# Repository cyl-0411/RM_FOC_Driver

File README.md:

# 更新日志

## [<1.2.0-beta>] - <2023.1.1>

### <电流采样方案更新>

* 变更	：更新为采集相电流

* 变更	：更新采样芯片

### <移除>

* 移除`MCU	`
* 将编码器独立到另一块`PCB`上

### <存在问题>

* 工作时电机会啸叫

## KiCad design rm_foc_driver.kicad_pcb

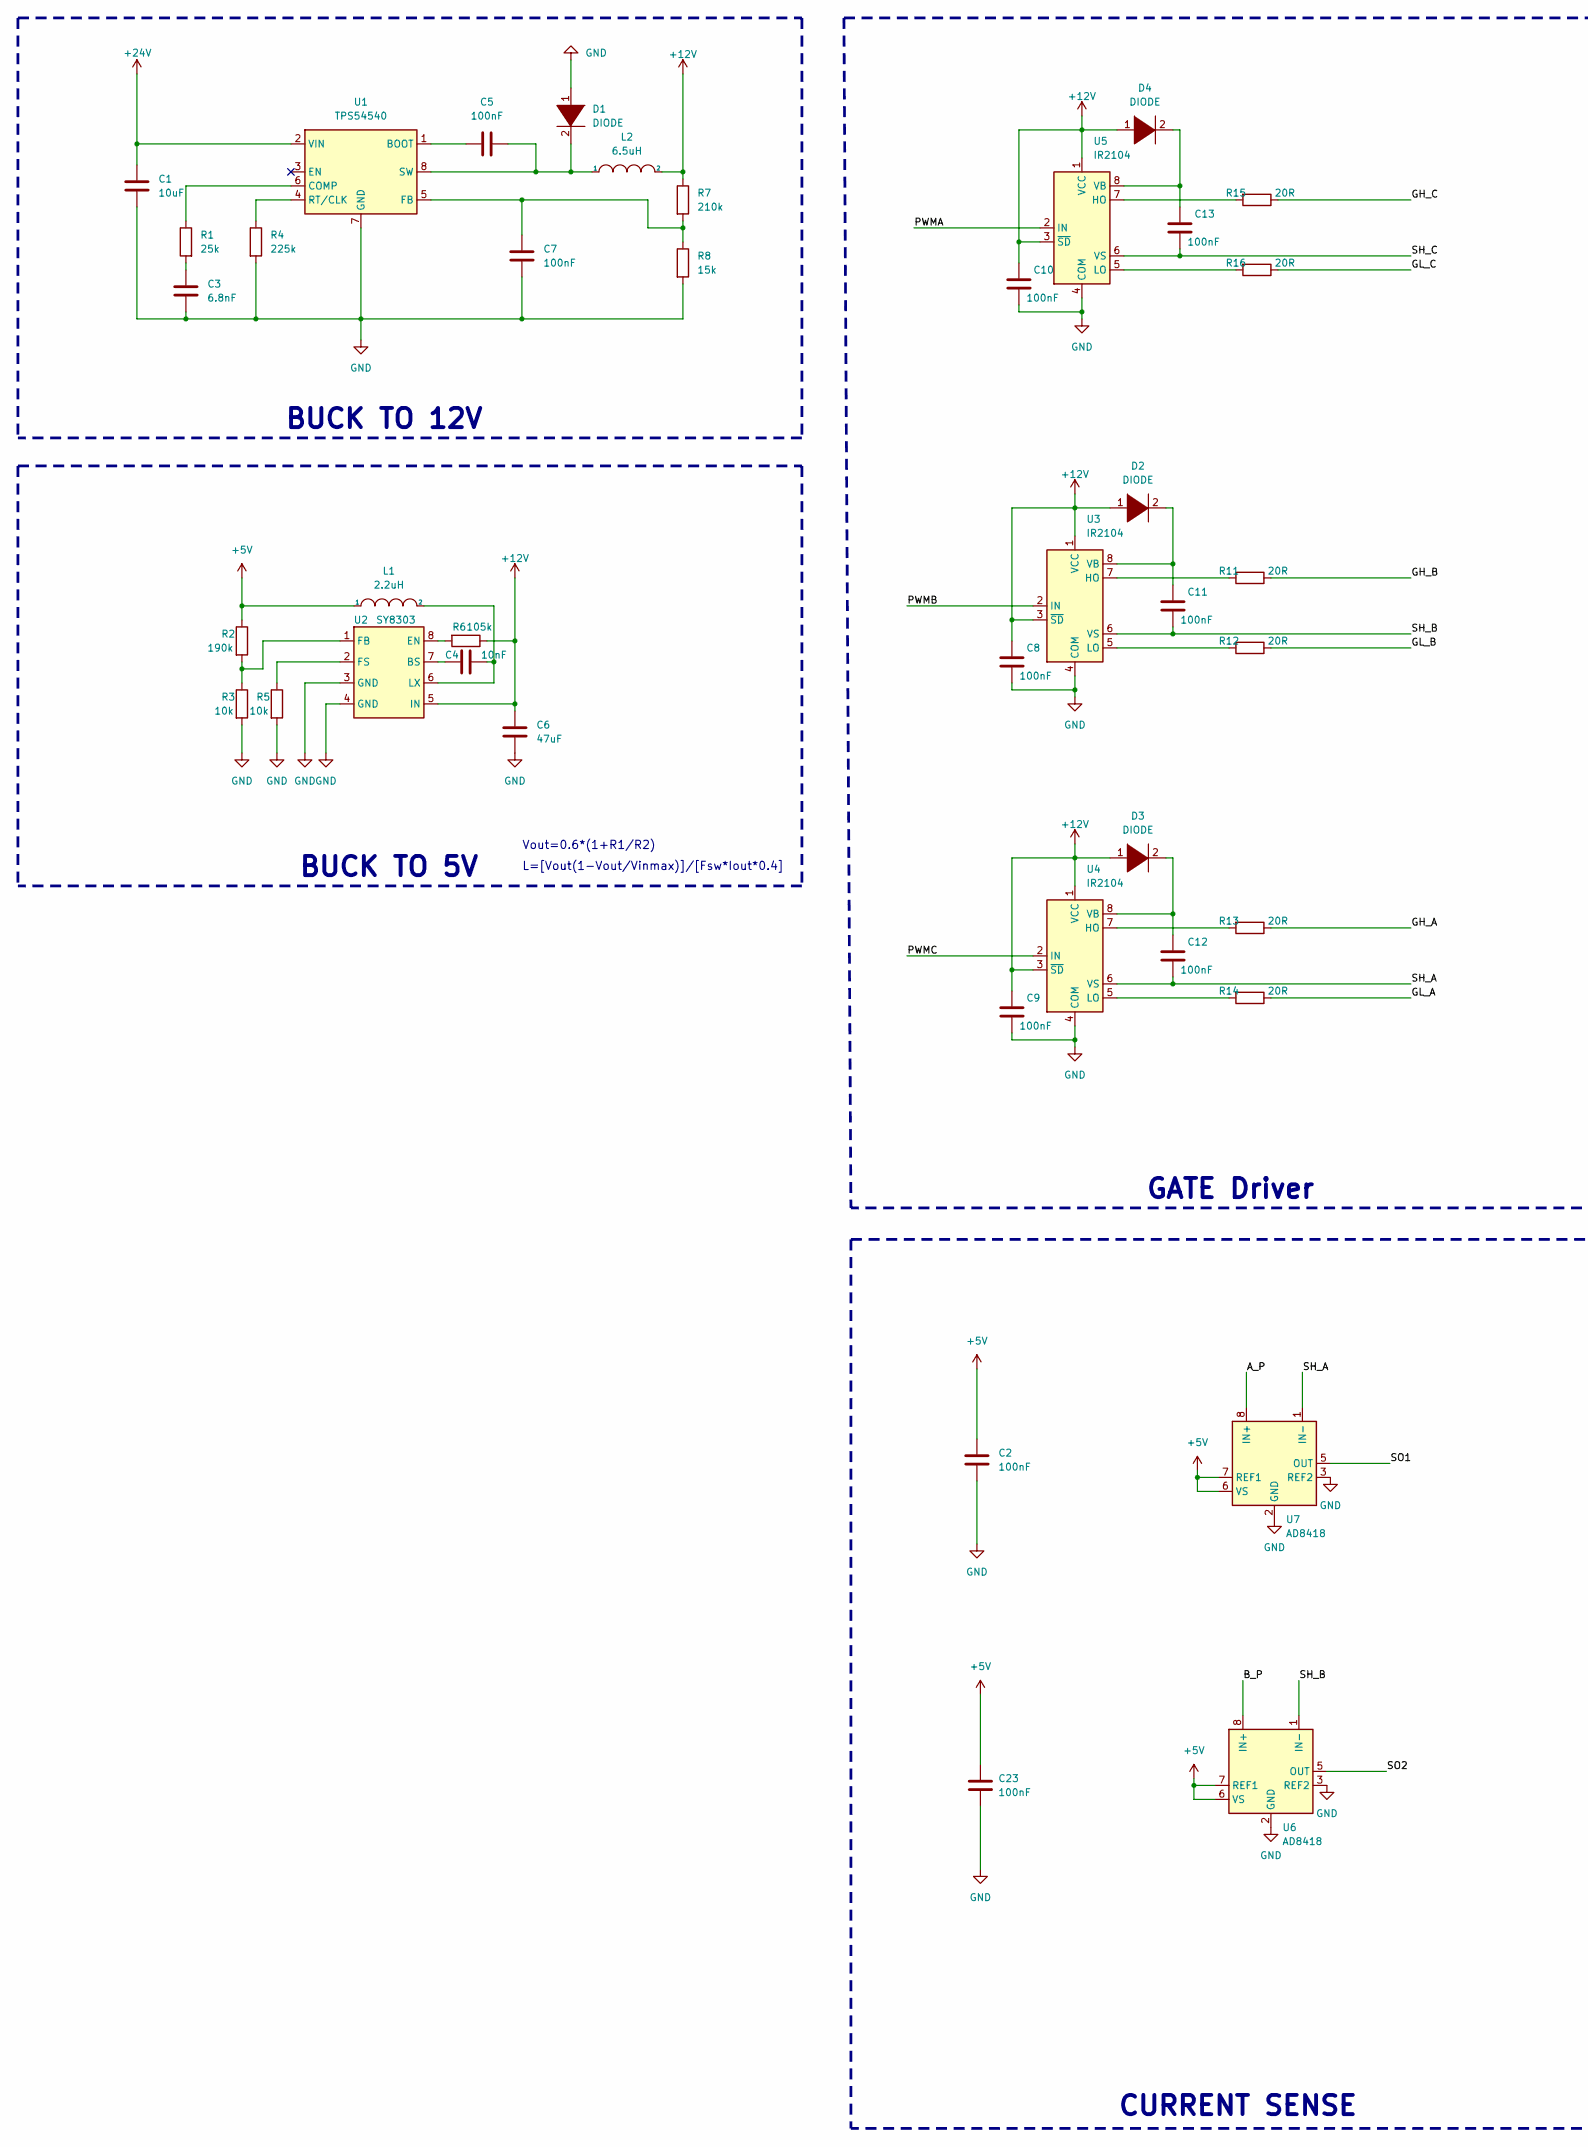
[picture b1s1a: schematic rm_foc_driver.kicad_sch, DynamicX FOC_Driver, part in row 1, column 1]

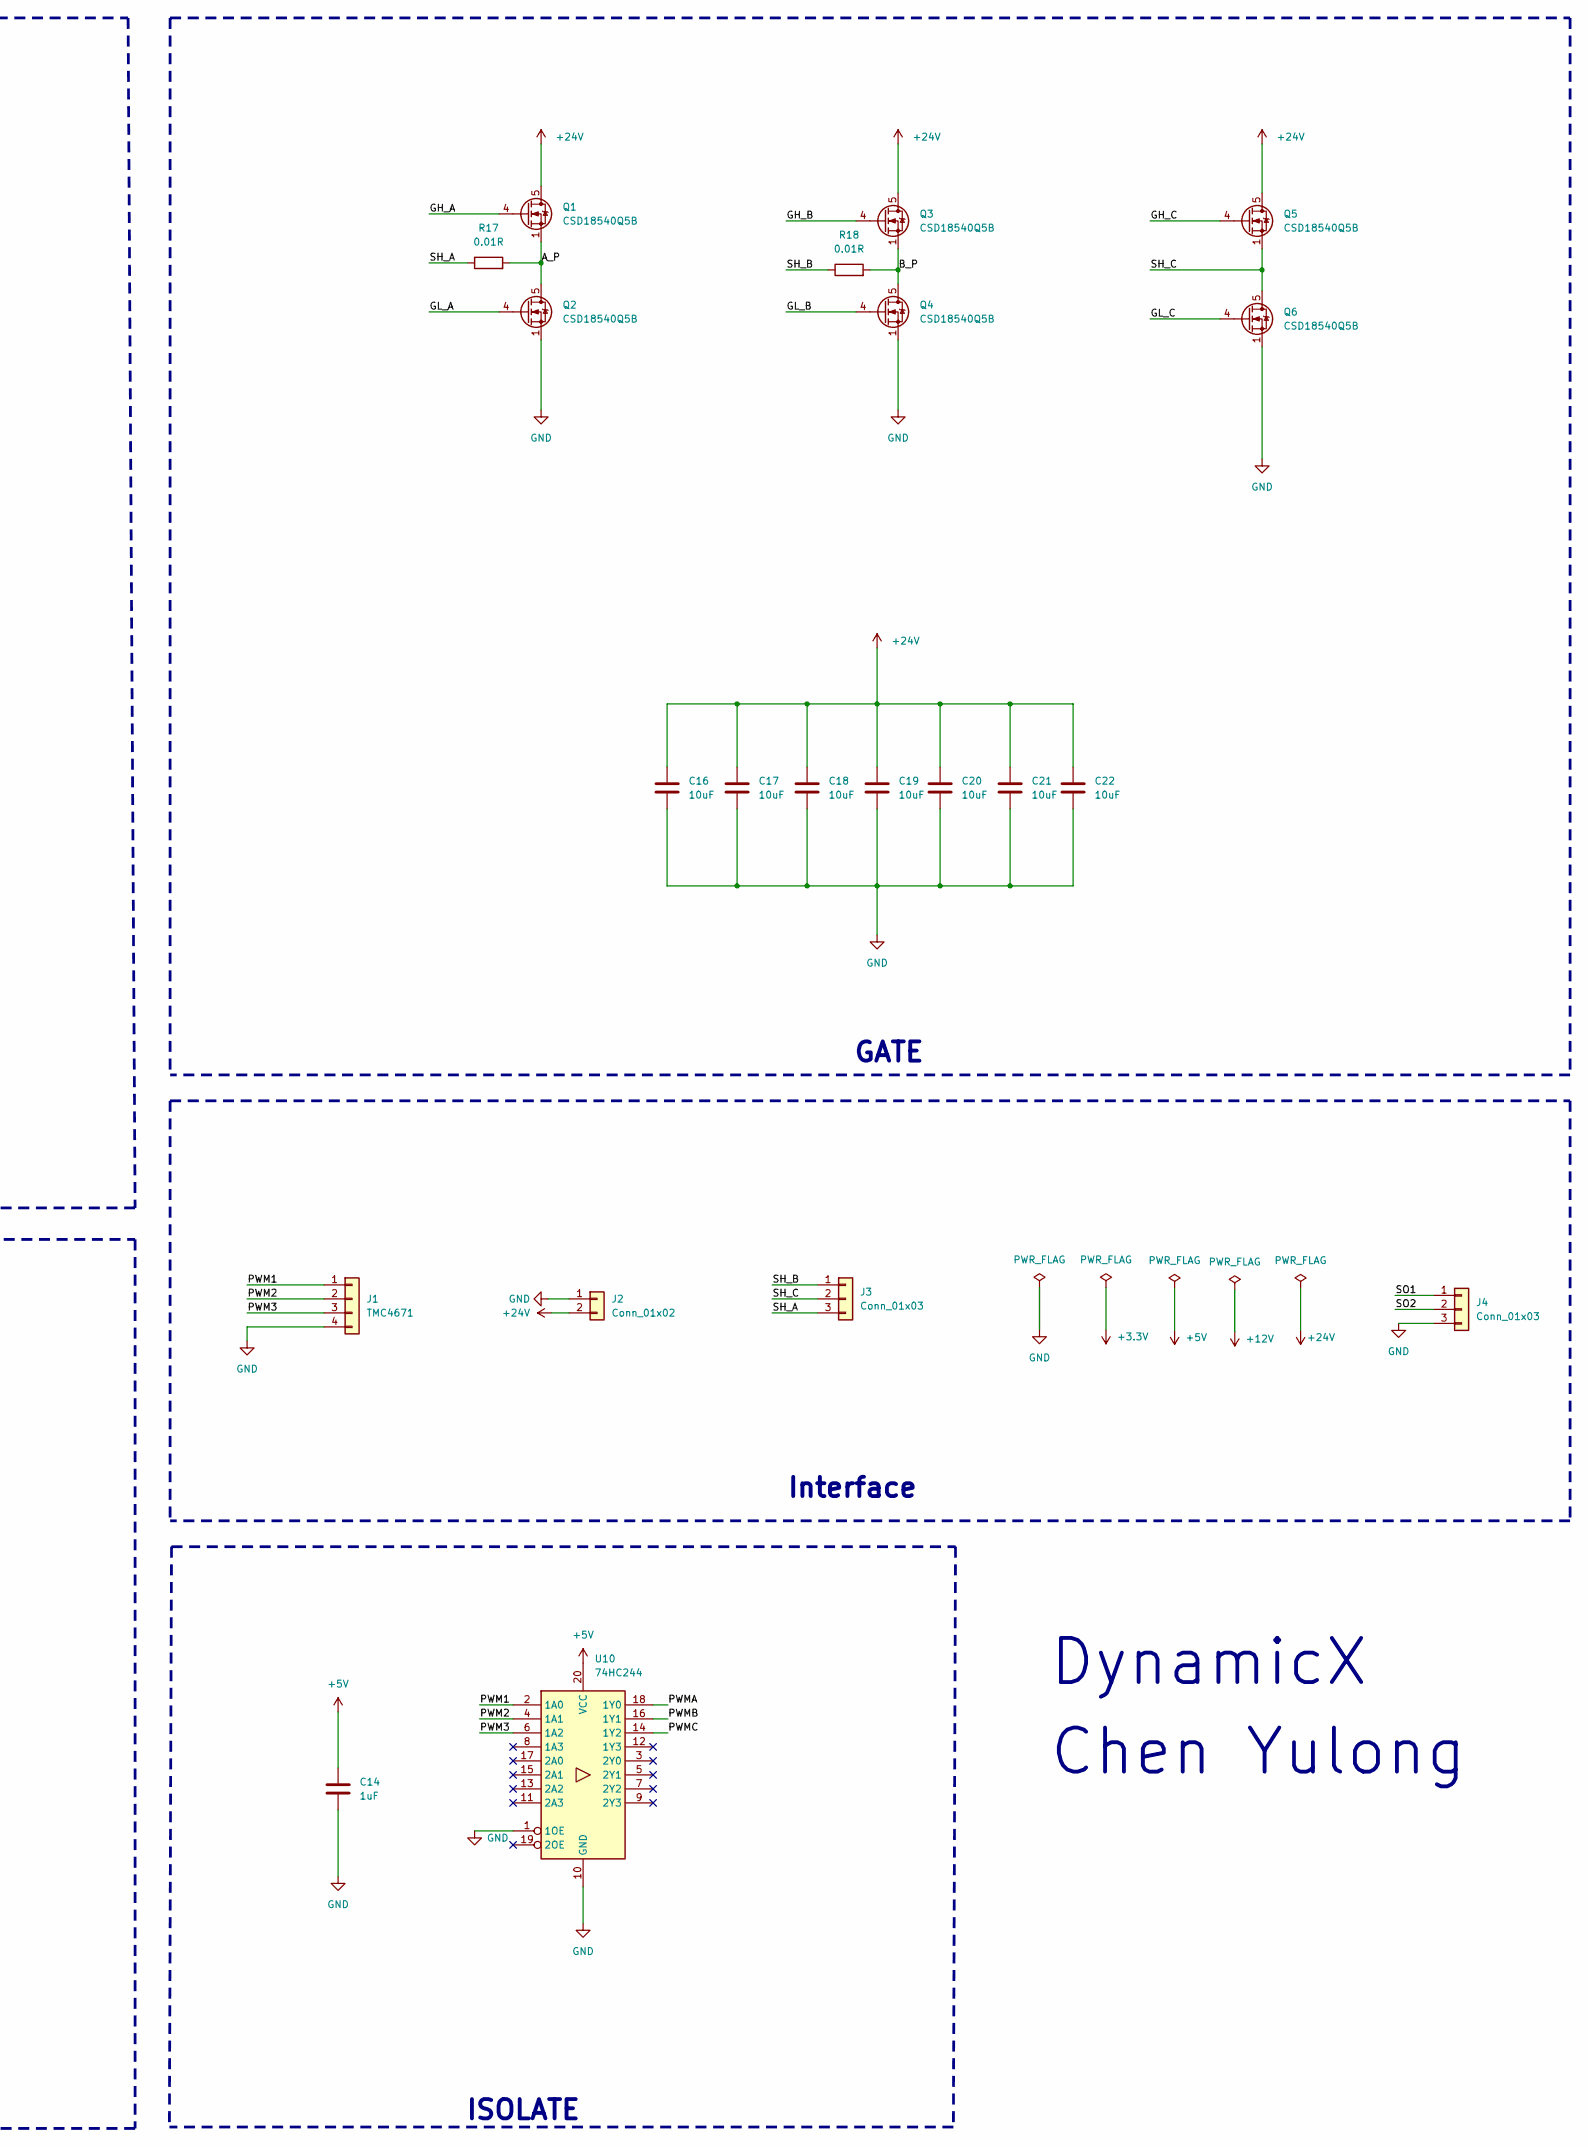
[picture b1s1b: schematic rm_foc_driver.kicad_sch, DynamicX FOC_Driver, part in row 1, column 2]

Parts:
C1, C16, C17, C18, C19, C20, C21, C22: 10uF; C_0805_2012Metric
C2, C5, C7, C8, C9, C10, C11, C12, C13, C23: 100nF; C_0603_1608Metric
C3: 6.8nF; C_0603_1608Metric
C4: 10nF; C_0603_1608Metric
C6: 47uF; C_0805_2012Metric
C14: 1uF; C_0603_1608Metric
D1, D2, D3, D4: DIODE; D_SOD-123
J1: TMC4671; PinHeader_1x04_P2.54mm_Vertical
J2: Conn_01x02; AMASS_XT30PW-M_1x02_P2.50mm_Horizontal
J3: Conn_01x03; AMASS_MR30PW-FB_1x03_P3.50mm_Horizontal
J4: Conn_01x03; PinSocket_1x03_P2.54mm_Vertical
L1: 2.2uH; L_Neosid_Ms42
L2: 6.5uH; L_Neosid_Ms42
Q1, Q2, Q3, Q4, Q5, Q6: CSD18540Q5B; TDSON-8-1
R1: 25k; R_0603_1608Metric
R2: 190k; R_0603_1608Metric
R3, R5: 10k; R_0603_1608Metric
R4: 225k; R_0603_1608Metric
R6: 105k; R_0603_1608Metric
R7: 210k; R_0603_1608Metric
R8: 15k; R_0603_1608Metric
R11, R12, R13, R14, R15, R16: 20R; R_0603_1608Metric
R17, R18: 0.01R; R_2512_6332Metric
U1: TPS54540; Texas_R-PDSO-G8_EP2.95x4.9mm_Mask2.4x3.1mm_ThermalVias
U2: SY8303; TSOT-23-8
U3, U4, U5: IR2104; SOP-8_3.9x4.9mm_P1.27mm
U6, U7: AD8418; SOP-8_3.9x4.9mm_P1.27mm
U10: 74HC244; TSSOP-20_4.4x6.5mm_P0.65mm

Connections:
+5V: C2.1, C14.1, C23.1, L1.1, R2.1, U6.6 (VS), U6.7 (REF1), U7.6 (VS), U7.7 (REF1), U10.20 (VCC)
+12V: C6.1, C8.1, C9.1, C10.1, D2.1 (K), D3.1 (K), D4.1 (K), L2.2, R6.1, R7.1, U2.5 (IN), U3.1 (VCC), U3.3 (~SD), U4.1 (VCC), U4.3 (~SD), U5.1 (VCC), U5.3 (~SD)
+24V: C1.1, C16.1, C17.1, C18.1, C19.1, C20.1, C21.1, C22.1, J2.2, Q1.5 (D), Q3.5 (D), Q5.5 (D), U1.2 (VIN)
/A_P: Q1.1 (S), Q1.2 (S), Q1.3 (S), Q2.5 (D), R17.2, U7.8 (IN+)
/B_P: Q3.1 (S), Q3.2 (S), Q3.3 (S), Q4.5 (D), R18.2, U6.8 (IN+)
/GH_A: Q1.4 (G), R13.1
/GH_B: Q3.4 (G), R11.1
/GH_C: Q5.4 (G), R15.1
/GL_A: Q2.4 (G), R14.1
/GL_B: Q4.4 (G), R12.1
/GL_C: Q6.4 (G), R16.1
/PWM1: J1.1, U10.2 (1A0)
/PWM2: J1.2, U10.4 (1A1)
/PWM3: J1.3, U10.6 (1A2)
/PWMA: U5.2 (IN), U10.18 (1Y0)
/PWMB: U3.2 (IN), U10.16 (1Y1)
/PWMC: U4.2 (IN), U10.14 (1Y2)
/SH_A: C12.2, J3.3, R17.1, U4.6 (VS), U7.1 (IN-)
/SH_B: C11.2, J3.1, R18.1, U3.6 (VS), U6.1 (IN-)
/SH_C: C13.2, J3.2, Q5.1 (S), Q5.2 (S), Q5.3 (S), Q6.5 (D), U5.6 (VS)
/SO1: J4.1, U7.5 (OUT)
/SO2: J4.2, U6.5 (OUT)
GND: C1.2, C2.2, C3.2, C6.2, C7.1, C8.2, C9.2, C10.2, C14.2, C16.2, C17.2, C18.2, C19.2, C20.2, C21.2, C22.2, C23.2, D1.1 (K), J1.4, J2.1, J4.3, Q2.1 (S), Q2.2 (S), Q2.3 (S), Q4.1 (S), Q4.2 (S), Q4.3 (S), Q6.1 (S), Q6.2 (S), Q6.3 (S), R3.2, R4.2, R5.2, R8.2, U1.7 (GND), U1.9 (GND), U2.3 (GND), U2.4 (GND), U3.4 (COM), U4.4 (COM), U5.4 (COM), U6.2 (GND), U6.3 (REF2), U7.2 (GND), U7.3 (REF2), U10.1 (1OE), U10.10 (GND)
unnamed: C3.1, R1.2
unnamed: C4.1, U2.7 (BS)
unnamed: C4.2, L1.2, U2.6 (LX)
unnamed: C5.1, U1.1 (BOOT)
unnamed: C5.2, D1.2 (A), L2.1, U1.8 (SW)
unnamed: C7.2, R7.2, R8.1, U1.5 (FB)
unnamed: C11.1, D2.2 (A), U3.8 (VB)
unnamed: C12.1, D3.2 (A), U4.8 (VB)
unnamed: C13.1, D4.2 (A), U5.8 (VB)
unnamed: R1.1, U1.6 (COMP)
unnamed: R2.2, R3.1, U2.1 (FB)
unnamed: R4.1, U1.4 (RT/CLK)
unnamed: R5.1, U2.2 (FS)
unnamed: R6.2, U2.8 (EN)
unnamed: R11.2, U3.7 (HO)
unnamed: R12.2, U3.5 (LO)
unnamed: R13.2, U4.7 (HO)
unnamed: R14.2, U4.5 (LO)
unnamed: R15.2, U5.7 (HO)
unnamed: R16.2, U5.5 (LO)

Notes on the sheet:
BUCK TO 12V
CURRENT SENSE
Chen Yulong
GATE Driver
Vout=0.6*(1+R1/R2)
GATE
BUCK TO 5V
Interface
DynamicX
L=[Vout(1-Vout/Vinmax)]/[Fsw*Iout*0.4]
ISOLATE

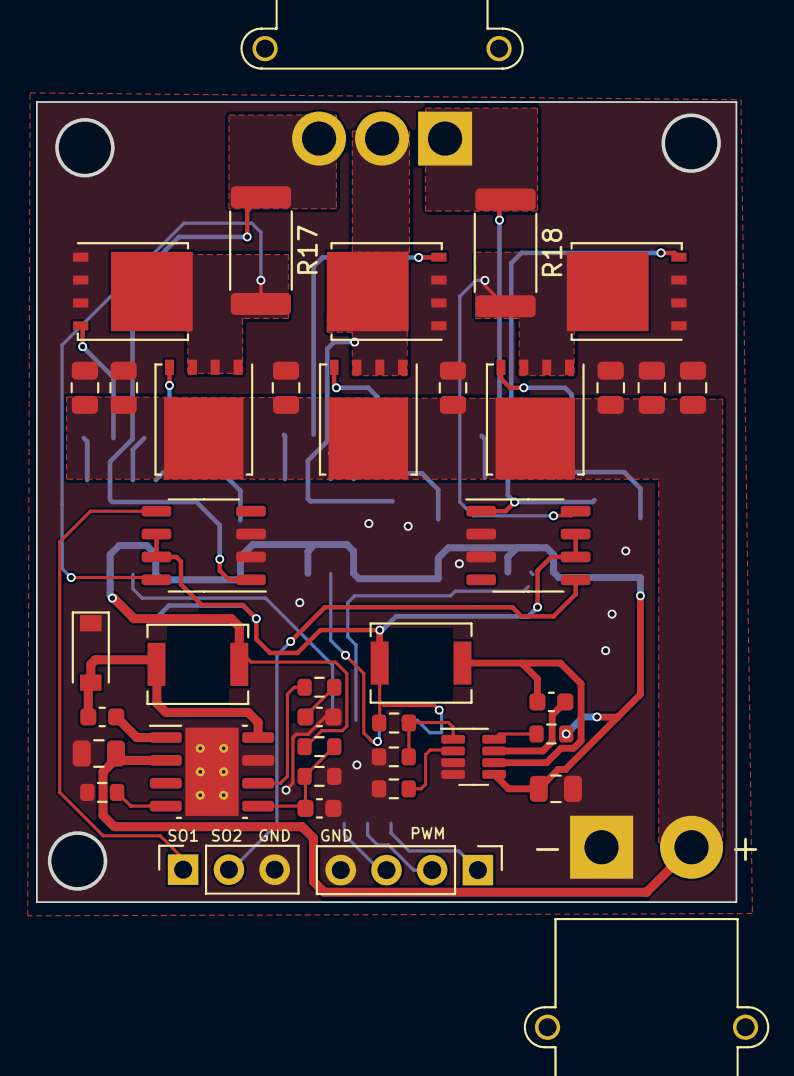
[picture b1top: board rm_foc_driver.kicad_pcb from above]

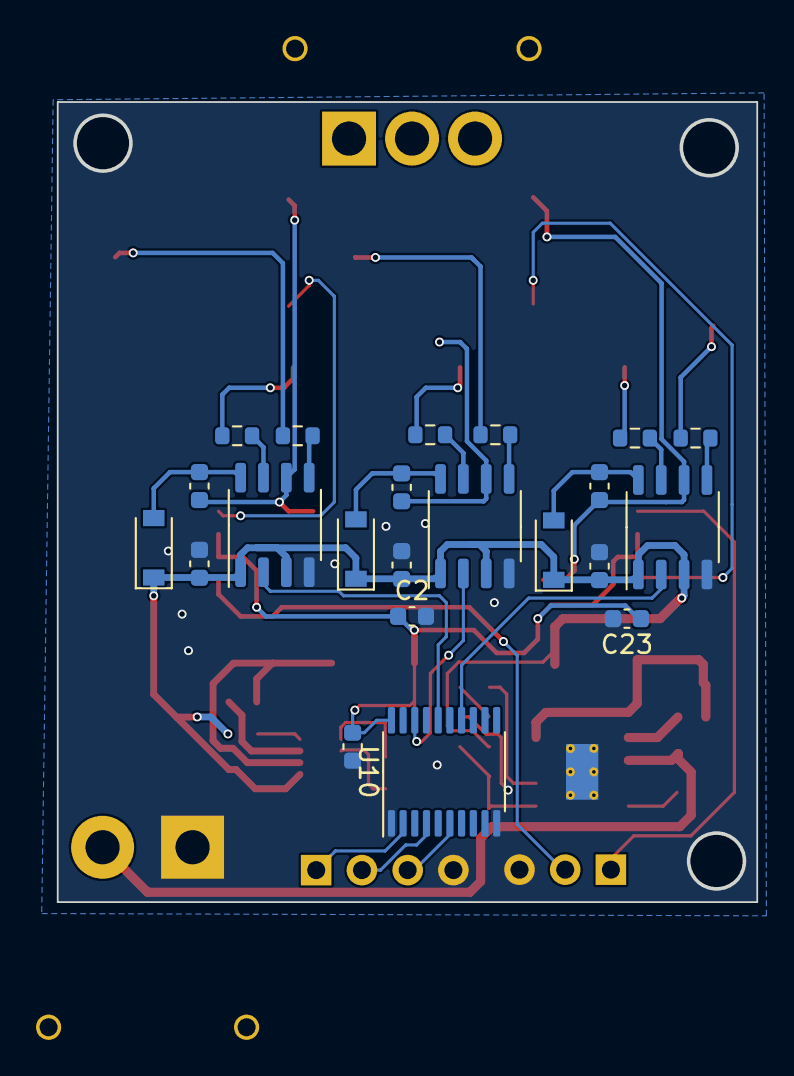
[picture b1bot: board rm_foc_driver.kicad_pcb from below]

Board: 2 copper layers, 38.9 x 44.5 mm, 62 parts (22 on the bottom side), 43 nets.

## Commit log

2022-08-08 Not complete yet
2022-08-10 new verson of pcb.ready to print
2022-08-27 Update pcb-layout.Not complete yet.Current progress 50%.
2022-08-27 Straight line version.
2022-08-30 Fcuk IRF7580 fuck fuck.csd18540 is better
2022-09-23 eg2133 guo le
2022-10-05 ir2104 version
2022-10-06 correct some bug yesterday
2022-10-14 add .gitignore
2022-10-18 update package
2022-10-29 version 1.1.0-beta
2022-10-29 version 1.0.0-beta
2022-10-31 version 1.0.0-beta.Round-angle PCB-layout
2023-01-07 remove mcu...
2023-01-11 20230111 AD8418
